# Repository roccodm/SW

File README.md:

# SW
Smart Working activity report

Nel 2020 l'Italia, causa covid, si accorge della possibilità di far lavorare in modalità agile. Si adotta, finalmente, ciò che all'estero era realtà da decenni: lo Smart Working: un'opzione lavorativa moderna che coniunga la flessibilità al raggiungimento degli obiettivi lavorativi.
Ci sono tonnellate di libri che spiegano in dettaglio quanto il benessere del lavoratore, specie chi svolge attività intellettive e creative, possa influire positivamente sui risultati professionali, eppure ad emergenza sanitaria peraltro non ancora pienamente superata, la governance morde pesantemente sul freno.
Con paradossi che il lavoratore che opera in regime smartworking debba rendicontare dettagliatamente la propria attività, spesso a differenza di chi lavora tradizionalmente in ufficio.

Se poi aggiungiamo altri due ingredienti: operare nel settore Pubblico spesso additato come fannullolandia e poi svolgere attività di Ricerca (che significa cercare, ma non sempre trovare risultati) il rischio concreto è di perdere la bussola e non capire se il lavoro che viene svolto andrà disperso o sarà tenuto in considerazione.

Su richiesta di fornire, nelle giornate in cui lavorerò in regime di smartworking, una dettagliata relazione di ciò che viene svolto ho quindi deciso, effettuando in significativa parte attività di sviluppo software, di iniziare a pushare su un apposito repository ogni cosa che produco. Si tratterà prevalentemente di codice per organizzare dataset costruiti in modo "non standard", algoritmi computativi, script di utility (magari anche per splittare file audio ad una certa posizione). In ogni listato cercherò in cima di illustrare, anche sommariamente, cosa fa o dovrebbe fare il singolo programma o script.

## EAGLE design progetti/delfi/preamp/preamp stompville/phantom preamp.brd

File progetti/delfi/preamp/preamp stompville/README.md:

This preamp is based on Stompville's circuit.
https://stompville.co.uk/?p=1306

Used 2N3819 with R10=3k3ohm (~0,6mA)

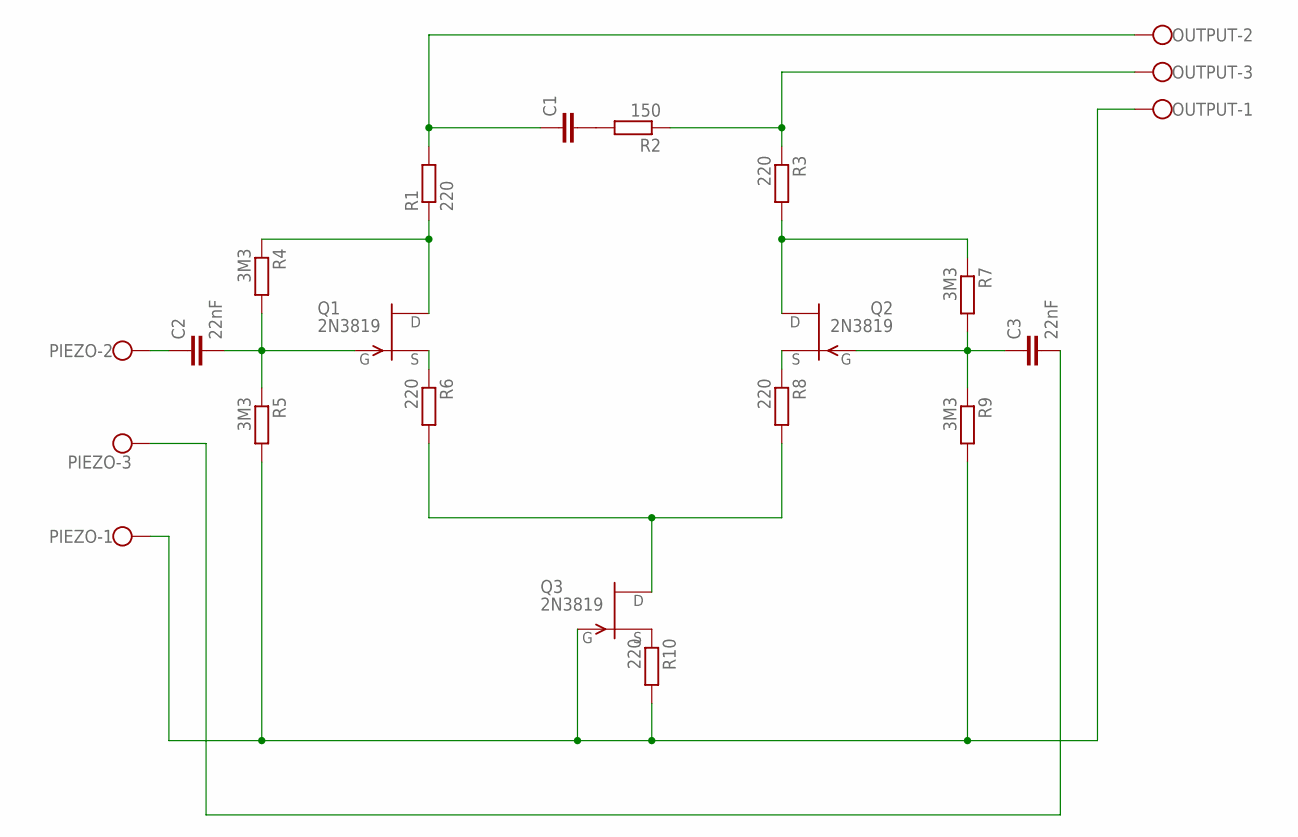
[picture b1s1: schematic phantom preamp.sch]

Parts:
C1: C-EU050-024X044; C050-024X044
C2, C3: 22nF; C050-024X044
OUTPUT: W237-103
PIEZO: W237-103
Q1, Q2, Q3: 2N3819; TO92
R1, R3, R6, R8, R10: 220; 0207/2V
R2: 150; 0207/2V
R4, R5, R7, R9: 3M3; 0207/2V

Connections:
unnamed: C2.2, Q1.2 (G), R4.2, R5.1
unnamed: Q1.3 (S), R6.1
unnamed: Q2.3 (S), R8.1
unnamed: Q3.3 (S), R10.1
unnamed: C3.1, Q2.2 (G), R7.2, R9.1
unnamed: C1.2, R2.2
unnamed: C2.1, PIEZO.2
unnamed: Q3.1 (D), R6.2, R8.2
unnamed: OUTPUT.1, PIEZO.1, Q3.2 (G), R5.2, R9.2, R10.2
unnamed: C3.2, PIEZO.3
unnamed: Q1.1 (D), R1.1, R4.1
unnamed: Q2.1 (D), R3.2, R7.1
unnamed: C1.1, OUTPUT.2, R1.2
unnamed: OUTPUT.3, R2.1, R3.1

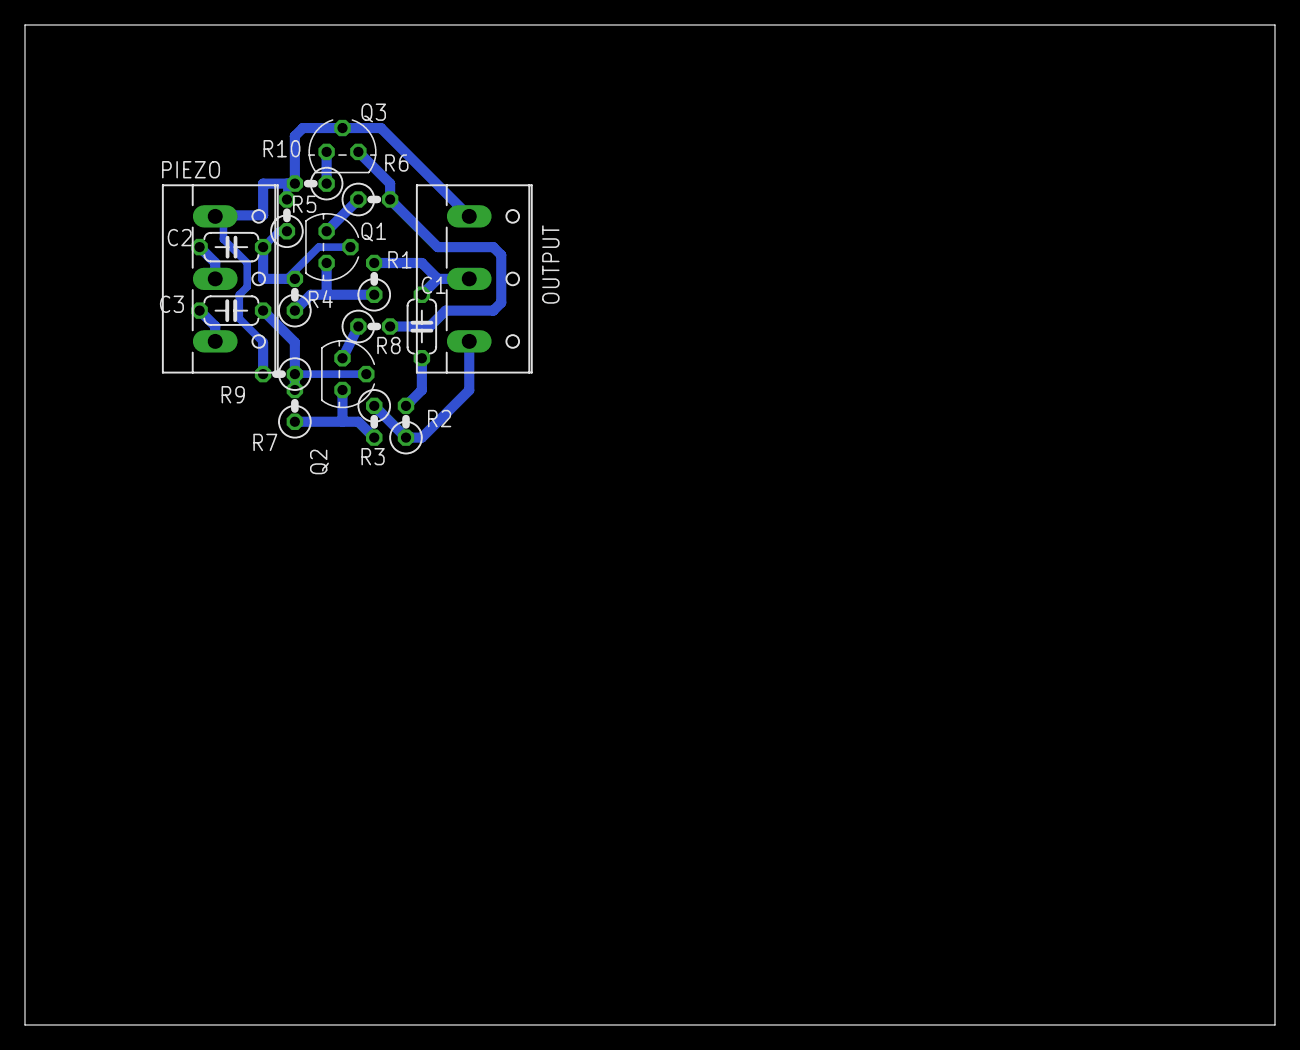
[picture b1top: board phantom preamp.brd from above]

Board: 2 copper layers, 100.0 x 80.0 mm, 18 parts (0 on the bottom side), 14 nets.

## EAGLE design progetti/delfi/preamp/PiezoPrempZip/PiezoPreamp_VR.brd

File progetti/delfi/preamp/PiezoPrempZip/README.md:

This circuit is based on LABIII's one published here: http://interface.khm.de/index.php/lab-log/piezo-disk-preamplifier/index.html

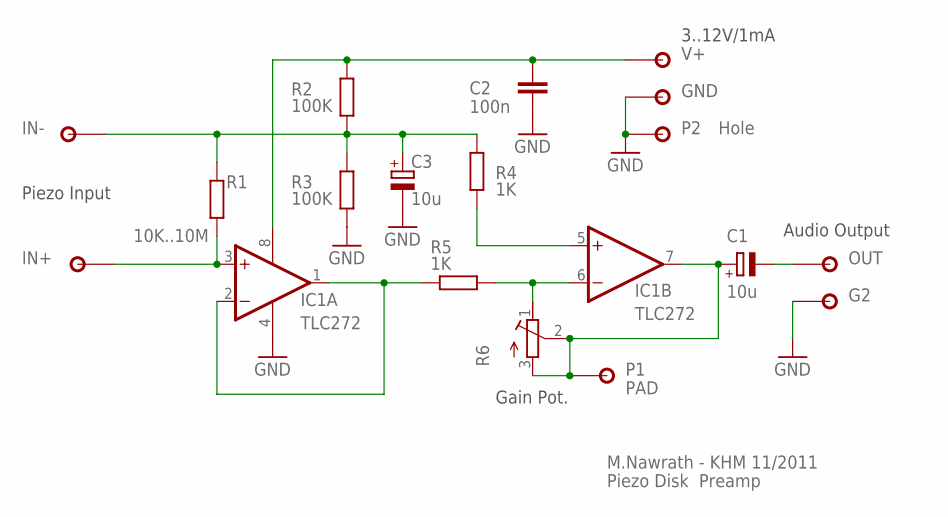
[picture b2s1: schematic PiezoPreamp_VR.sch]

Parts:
C1, C3: 10u; E2,5-5
C2: 100n; C025-025X050
G2: PAD1,46MM; PAD146
GND: PAD1,46MM; PAD146
IC1: TLC272; DIL08
IN+: PAD1,46MM; PAD146
IN-: PAD1,46MM; PAD146
OUT: PAD1,46MM; PAD146
P1: PAD; PAD127L1
P2: Hole; PAD146
R1: 10K..10M; 0207/10
R2, R3: 100K; 0207/10
R4, R5: 1K; 0207/10
R6: R-TRIMM3006P; RTRIM3006P
V+: PAD1,46MM; PAD146

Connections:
GND: C2.1, C3.-, G2.1, GND.1, IC1.4 (V-), P2.1, R3.1
unnamed: IC1.6 (-IN), R5.1, R6.1 (E)
unnamed: C1.-, OUT.1
unnamed: IC1.5 (+IN), R4.1
unnamed: C1.+, IC1.7 (OUT), P1.P$2, R6.2 (S), R6.3 (A)
unnamed: IC1.1 (OUT), IC1.2 (-IN), R5.2
unnamed: IC1.3 (+IN), IN+.1, R1.1
unnamed: C3.+, IN-.1, R1.2, R2.2, R3.2, R4.2
V9V: C2.2, IC1.8 (V+), R2.1, V+.1

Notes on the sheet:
Piezo Disk Preamp
M.Nawrath - KHM 11/2011
Audio Output
Piezo Input
3..12V/1mA
Gain Pot.

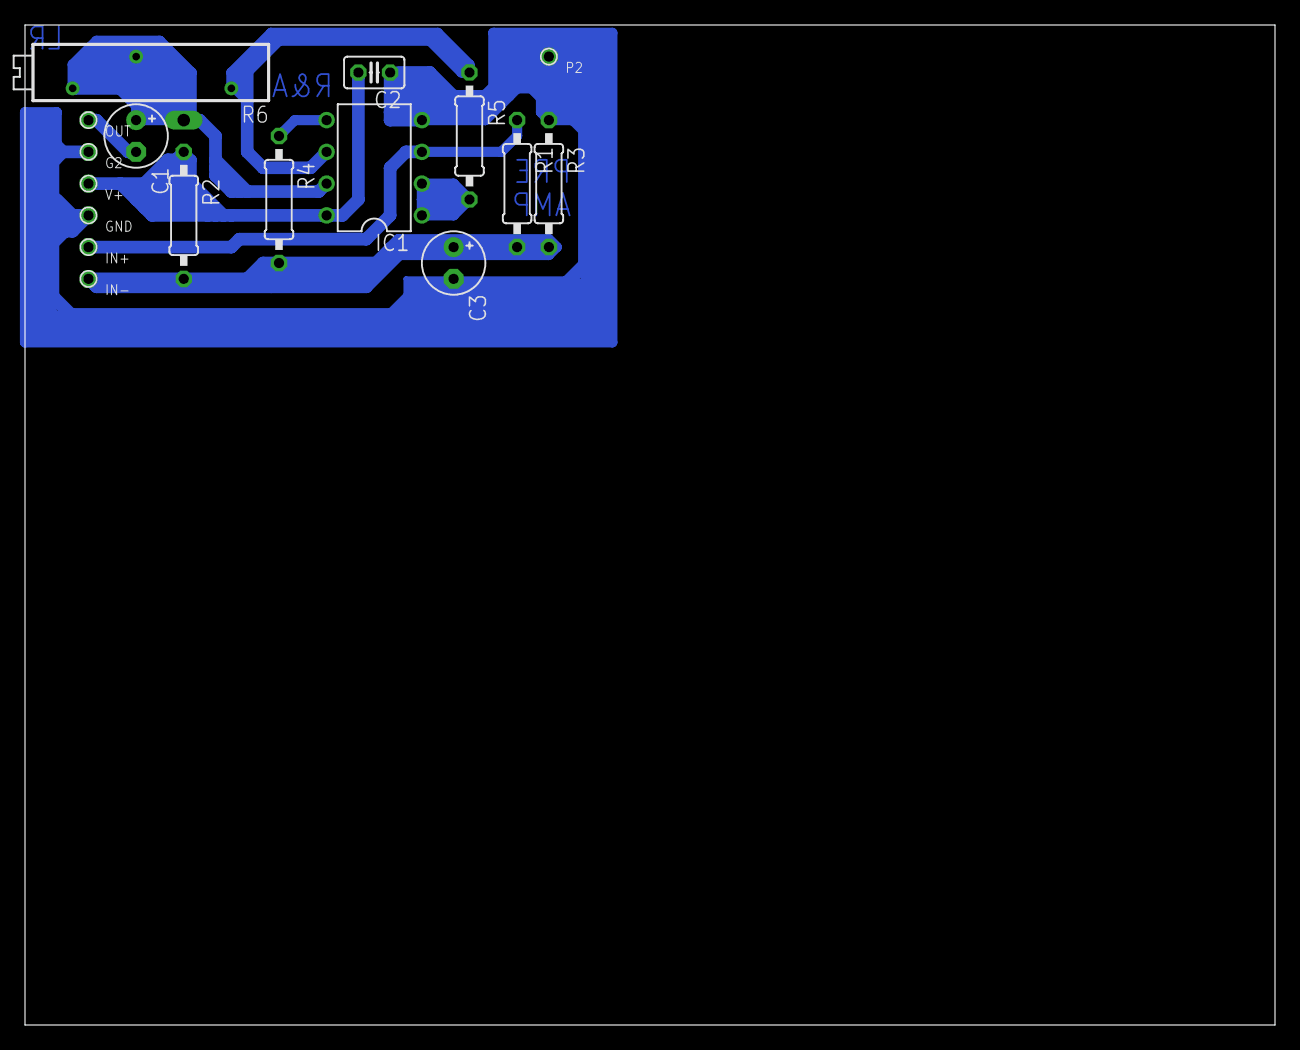
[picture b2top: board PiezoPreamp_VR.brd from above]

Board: 2 copper layers, 100.0 x 80.0 mm, 18 parts (0 on the bottom side), 9 nets.

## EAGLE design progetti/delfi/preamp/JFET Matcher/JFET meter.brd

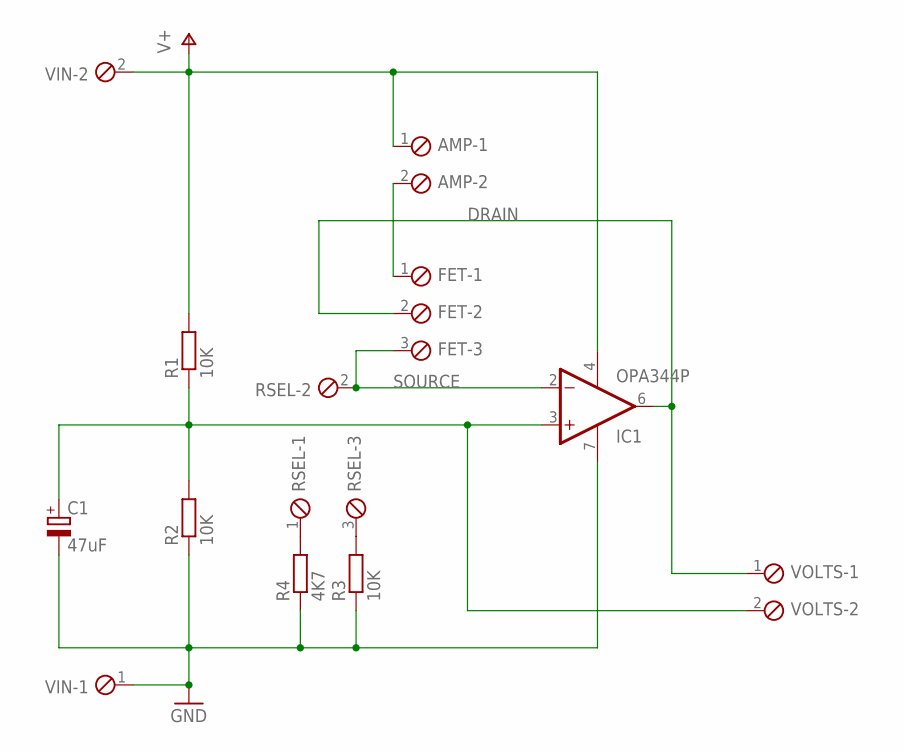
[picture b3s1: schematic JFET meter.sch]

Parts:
AMP: MPT2; 2POL254
C1: 47uF; E5-10,5
FET: MPT3; 3POL254
IC1: OPA344P; DIL08
R1, R2, R3: 10K; 0207/10
R4: 4K7; 0207/10
RSEL: MPT3; 3POL254
VIN: MPT2; 2POL254
VOLTS: MPT2; 2POL254

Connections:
DRAIN: AMP.2, FET.1
GND: C1.-, IC1.7 (V+), R2.1, R3.1, R4.1, VIN.1
unnamed: C1.+, IC1.3 (+IN), R1.1, R2.2, VOLTS.2
unnamed: FET.2, IC1.6 (OUT), VOLTS.1
unnamed: R4.2, RSEL.1
unnamed: R3.2, RSEL.3
SOURCE: FET.3, IC1.2 (-IN), RSEL.2
V+: AMP.1, IC1.4 (V-), R1.2, VIN.2

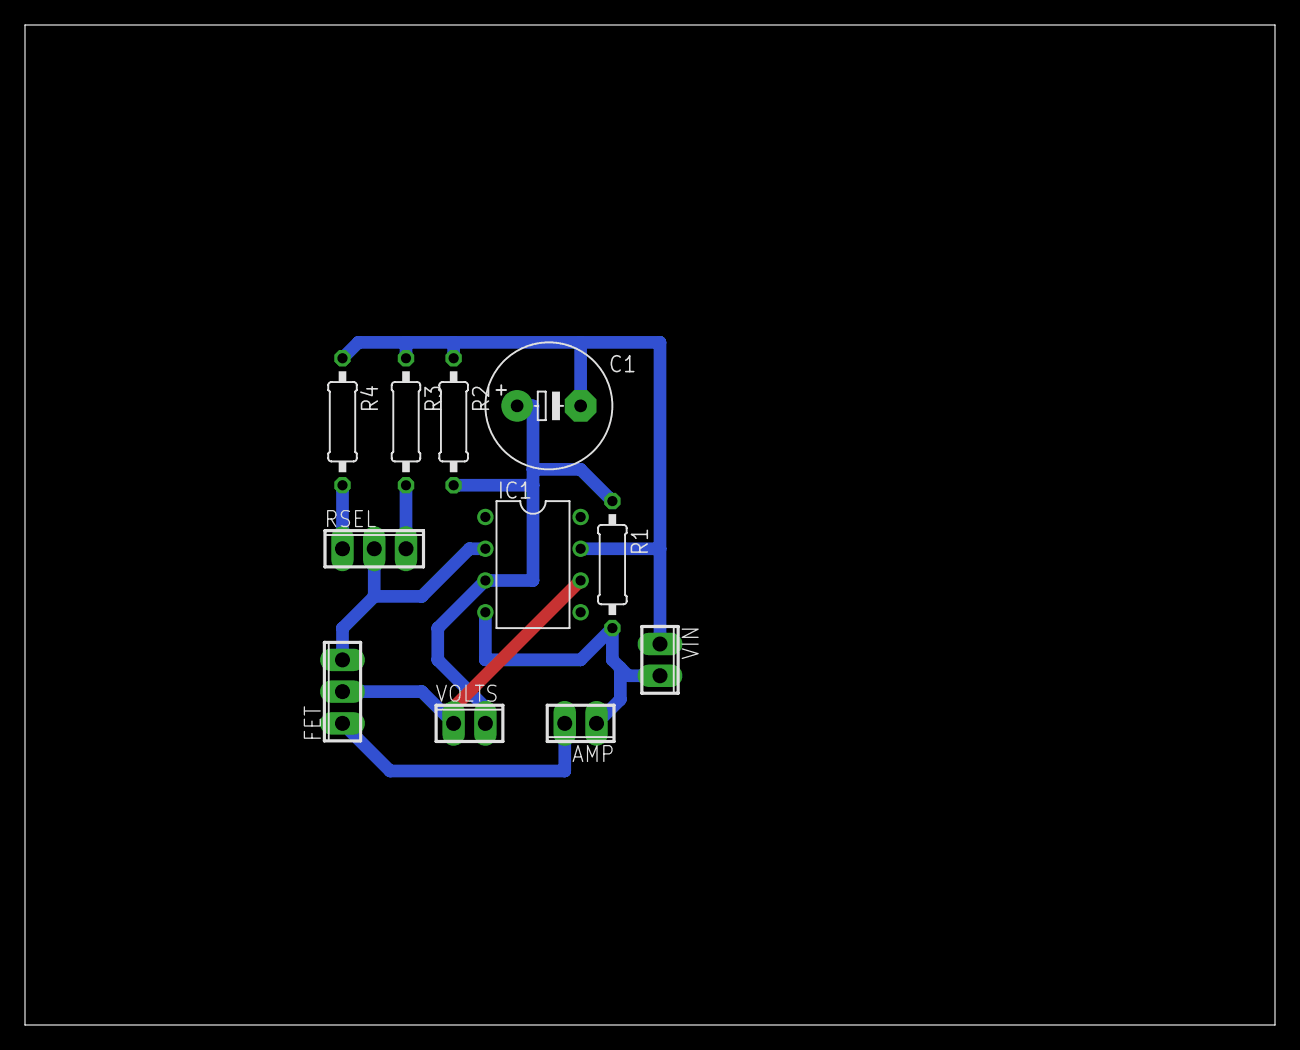
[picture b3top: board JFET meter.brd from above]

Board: 2 copper layers, 100.0 x 80.0 mm, 11 parts (0 on the bottom side), 8 nets.

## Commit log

2022-03-31 Update multiple_excel_files_to_one_csv.py
    Minor fixes
2022-03-31 Riorganizzazione directory
2022-03-31 Inserito tree con gli articoli in preparazione
2022-04-12 aggiunto progetti
2022-04-12 aggiunto script per grafici per la conferenza geologia di torino
2022-04-12 Esempio di grafico per la conferenza geologia di torino
2022-04-19 Primo tentativo di client jack scritto in c
2022-04-19 aggiungo thread per gestione connessione socket
2022-04-19 inserita nuova modalità di gestione della memoria implementando ex-novo delle code circolari
2022-04-19 Prima versione funzionante client-server
2022-04-21 prima release funzionante del middleware
2022-04-21 aggiunto tip per compilazione
2022-04-21 impoved ringbuffer.c
2022-04-21 improved jackclient.c
2022-04-21 More mature version
2022-04-26 aggiunta utility di rendicontazione attraverso git
2022-04-26 Script per elaborazione dati e generazione grafici per articolo PER3-PERSEUS IPA
2022-04-27 Tool per estrazioni dati schede report db delfi
2022-05-06 Schemi del JFET matcher
2022-05-06 Aggiunto schema del preamplificatore single ended
2022-05-09 aggiunto circuito preamp phantom powered
